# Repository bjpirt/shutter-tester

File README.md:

# Shutter Tester

A low cost but capable three-point shutter speed tester that runs on ESP32. It uses the PCB design to provide the physical structure of the tester so that all you need to do is solder it together and all of the mechanical design is taken care of.
It runs on ESP32 so is easily updated using the Arduino platform. The project is 100% open source (see the [license file](LICENSE.md) for details).
The UI runs in the browser and communicates with the shutter tester via Bluetooth - you can try out the UI [here](https://bjpirt.github.io/shutter-tester/?demo=true).

## Design

The design of the shutter tester is quite simple; it uses three IS485E / IS486E light sensors with built-in amplifiers to trigger three digital input interrupts on the ESP32 MCU. I wanted to keep the front side of the PCB clear to avoid it ever scratching the camera body so have opted for using surface mount components. I've used quite large packages for these so that they can be more easily hand soldered. The ESP32 uses an "ESP32 C3 Super Mini" module which is very small, can be surface mounted and has USB C built-in which can be used to power the whole board. I've kept the PCB size down to 50mm so that you can take advantage of low cost PCB fabrication. There are silk-screen markings to help position the tester over the camera shutter and three large holes to help see the edges from behind. It should either be taped in place or held with an elastic band.

The sensor has a Bluetooth connection and you can connect this to Chrome to use quite a capable web interface so you can get a lot of detail on the calibration. You can try out the UI [here](https://bjpirt.github.io/shutter-tester/?demo=true)

## Bill of materials

The BoM is quite low cost and relatively minimal:

- 1 x ESP32 C3 Super Mini module
- 3 x IS485E light sensor
- 6 x 1k 1206 SMD Resistor
- 3 x 2k 1206 SMD Resistor
- 3 x 0.01uF 1206 SMD Capacitor

## Assembly

The main thing to take care over during assembly is to ensure the lens of the light sensor aligns to the small hole in the PCB that allows the light through. The three legs of the sensor should be bent down slightly so that they can solder onto the three pads on the PCB.

The capacitors and resistors can be easily hand soldered (a finer soldering iron tip helps here) by applying solder to one of the pads on the PCB, using tweezers, solder one end of the component to the soldered pad on the PCB, then solder the other end once it is held in place. If you're experienced in surface mounting you could always use solder paste, but it's pretty straightforward without this. There are markings on the board for which component goes where (C1, C2 and C3 for the capacitors, Resistor values are marked 1k and 2k). The capacitors are optional and may be removed in a future iteration.

It's best to test the ESP32 module before soldering to ensure it's working fine. Program this using the sketch included and make sure it is outputting "Ready to measure" on the serial console (running at 921600 baud).

It's a good idea to place some black insulation tape over the back of the sensors otherwise stray light can cause false readings.

## Usage

Attach the shutter tester behind the shutter of the camera (I normally use 2 - 3 small blobs of Blu-Tak which works well). You can use the three larger holes in the tester to align with the edges of the shutter aperture. Open the shutter once you've this so you can check it's properly positioned by setting the shutter to "Bulb" and opening it. Remove the lens (if possible) and place a strong, even light at the front of the camera. You can use a full size bulb for this so long as it is the type that has a white diffuser bulb, not clear. Basically you want to ensure that light can pass directly through the three holes to reach the sensors, not at an angle. I've also had good results with a small USB powered LED panel.

### Using Bluetooth

There is a user interface that connects to the ESP32 from a Chrome web browser directly and lets you analyse all of the measurements quite easily.

You can easily use the [latest version](https://bjpirt.github.io/shutter-tester/). You should then be able to click the `Connect` button and pair with your shutter tester using Bluetooth. Select the speed you want to test, set up the light and fire the shutter. The new reading should appear in the table.

If you want to just try out the UI without a tester, you can use [this link](https://bjpirt.github.io/shutter-tester/?demo=true) and the "Test" button will simulate a shutter being fired. From a privacy perspective, the UI runs entirely in your browser and nothing goes over the internet.

If you want to run this locally you can do the following:

- Install Node.js (v22)
- Open a terminal in the `ui` folder of this repository
- run `npm install`
- run `npm run dev`
- Go to the URL printed in your terminal ([http://localhost:5173/](http://localhost:5173/))

### Using serial

Open a serial terminal to the ESP32 (this is built in to the Arduino IDE). You'll need to connect at 921600 baud.

Fire the shutter and it will print out the timings to the serial console. There are two sets of timings:

- The time taken for each shutter to travel across the frame - it's important to try and get both shutters moving at around the same speed
- The time each sensor was exposed for in microseconds, milliseconds and fractions of a second

```
Ready to measure

Shutter timing
Shutter 1: 1-2: 16582 uS || 2-3: 12632 uS
Shutter 2: 1-2: 23756 uS || 2-3: 18462 uS

Exposure timing
Sensor 1: 4346 uS || 4.3 mS || 1 / 228
Sensor 2: 5028 uS || 5.0 mS || 1 / 198
Sensor 3: 5528 uS || 5.5 mS || 1 / 182
```

In this example, the time taken for the first shutter to travel between the first and second (centre) sensors was 16582 microseconds and 12632 microseconds between the second (centre) and third sensor. You can see that in this example the second shutter is slow and would need adjusting.

Looking at the exposure time at each sensor, you can see the timings would need adjusting to give a good even exposure. First you would adjust the shutter timings to try and get them similar and then adjust both shutter tensioners to get the exposure time to match the expected (in this case it should have been 1/250 S)

# To Do

- [ ] Calculate variations across shutter and whether they are within tolerances
- [ ] Add graph visualisation of shutter speeds
- [ ] Generate report from three point test
- [x] Enable detailed measurements to be shown / hidden in three point mode
- [x] Deploy to GitHub pages using GitHub actions
- [x] Automatically work out vertical or horizontal shutter
- [x] Display full shutter timing
- [x] Separate shutter timing mode
- [x] Single shot mode (only show last shot timing) - useful for initial tuning
- [x] Compensation for sensor width

## Future

- [ ] Add persistence in the browser to enable common presets to be stored - e.g. camera types with speeds
- [ ] Enable different "runs" to be stored and compared so you can see progression when adjusting
- [ ] Add exposure measurement with light to frequency sensor
- [ ] Investigate reflective measurement from front of camera for e.g. Barnack Leicas
- [ ] Investigate using an analog photodiode instead of a binary sensor

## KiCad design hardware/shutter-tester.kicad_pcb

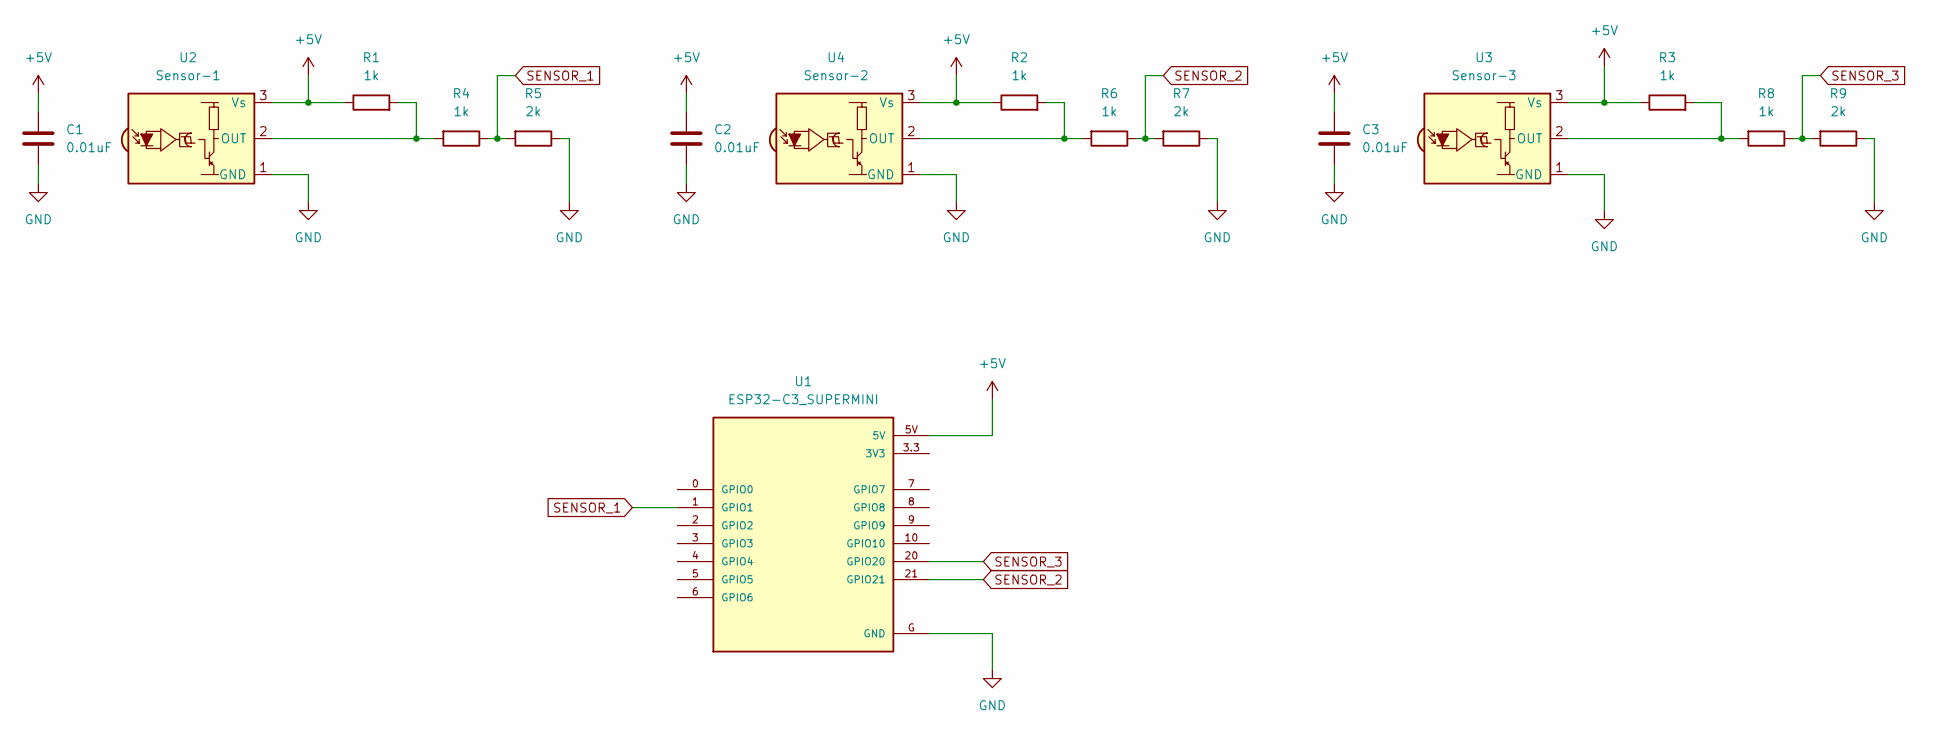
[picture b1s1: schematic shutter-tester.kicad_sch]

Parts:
C1, C2, C3: 0.01uF; C_1206_3216Metric_Pad1.33x1.80mm_HandSolder
R1, R2, R3, R4, R6, R8: 1k; R_1206_3216Metric_Pad1.30x1.75mm_HandSolder
R5, R7, R9: 2k; R_1206_3216Metric_Pad1.30x1.75mm_HandSolder
U1: ESP32-C3_SUPERMINI; MODULE_ESP32-C3_SUPERMINI_SMT
U2: Sensor-1; Sharp_IS485_Flat_Mount
U3: Sensor-3; Sharp_IS485_Flat_Mount
U4: Sensor-2; Sharp_IS485_Flat_Mount

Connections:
+5V: C1.2, C2.1, C3.2, R1.1, R2.1, R3.1, U1.5V, U2.3 (Vs), U3.3 (Vs), U4.3 (Vs)
GND: C1.1, C2.2, C3.1, R5.1, R7.1, R9.1, U1.G (GND), U2.1 (GND), U3.1 (GND), U4.1 (GND)
unnamed: R1.2, R4.2, U2.2 (OUT)
unnamed: R3.2, R8.2, U3.2 (OUT)
unnamed: R2.2, R6.2, U4.2 (OUT)
SENSOR_1: R4.1, R5.2, U1.1 (GPIO1)
SENSOR_2: R6.1, R7.2, U1.21 (GPIO21)
SENSOR_3: R8.1, R9.2, U1.20 (GPIO20)

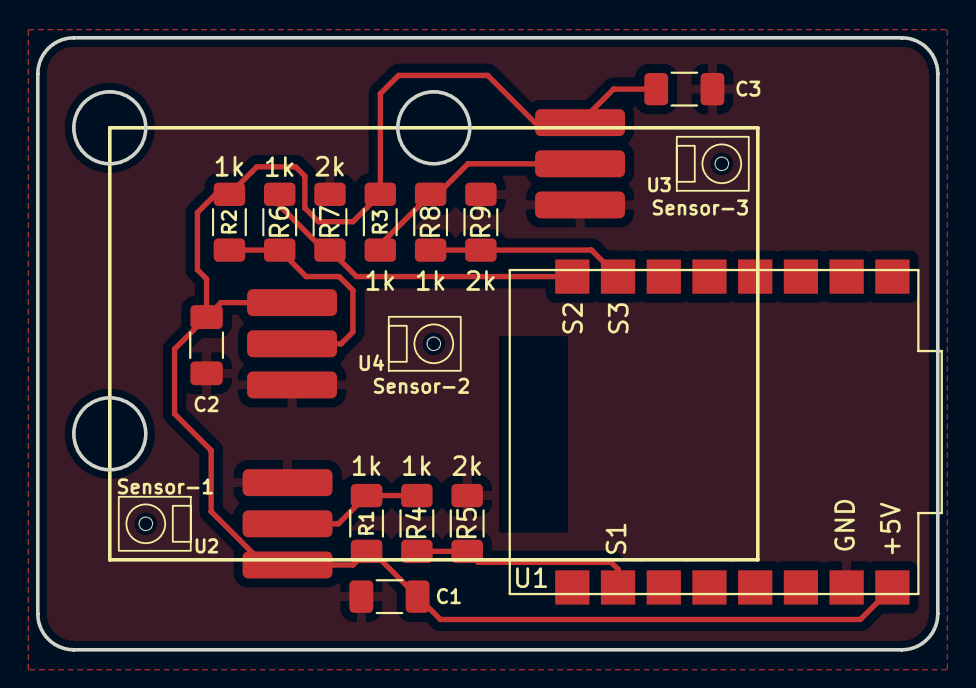
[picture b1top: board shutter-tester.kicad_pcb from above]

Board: 2 copper layers, 50.0 x 34.0 mm, 16 parts (0 on the bottom side), 8 nets.

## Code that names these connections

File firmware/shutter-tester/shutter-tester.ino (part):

#define LED 8
#define SENSOR_1 1
#define SENSOR_2 21
#define SENSOR_3 20

#define VERSION "2.2.0"

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  Serial.println("");
  Serial.println("Ready to measure");
  pinMode(LED, OUTPUT);
  pinMode(SENSOR_1, INPUT);
  pinMode(SENSOR_2, INPUT);
  pinMode(SENSOR_3, INPUT);
  attachInterrupt(SENSOR_1, sensor1_isr, CHANGE);
  attachInterrupt(SENSOR_2, sensor2_isr, CHANGE);
  attachInterrupt(SENSOR_3, sensor3_isr, CHANGE);
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
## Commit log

2025-01-24 Initial commit of project
2025-01-27 fix: groundplane issue w/ 2 via in PCB; update pictures
2025-01-28 v2.0 of the hardware
2025-01-31 Initial spike of Web Bluetooth UI
2025-01-31 Don't use GPIO 0 for sensor input
2025-02-18 More detail on the measurements
2025-02-18 Add ability to reset all measurements and clear individual ones
2025-02-18 v2.1 of the PCB
2025-02-22 Add the bluetooth firmware
2025-02-22 Add a header to the ui
2025-02-22 Rework the data display to use a single table
2025-03-02 Update the docs for the bluetooth UI
2025-03-02 Initial changes to support different modes for the shutter tester
2025-03-03 Enable the mode to be set on the sensor via Bluetooth
2025-03-06 Add to do list in Readme
2025-03-06 Change the page title from the default
2025-03-06 Display one decimal place in 1/X s timing display for accuracy
2025-03-06 Use 'timing' instead of 'data'
2025-03-07 Add initial implementation of sensor width compensation
2025-03-21 Add in full side to side shutter timings
2025-03-21 Fix the compensation algorithm and make it apply to summary rows
2025-03-21 Refactor the three point measurements page to be more self contained
2025-03-22 Wire up the different pages with an internal message bus
2025-03-22 Add shutter timing view and reorganise the settings
2025-03-22 Add a shot by shot mode
2025-04-10 Enable the shutter direction to be set for accurate compensation
2025-07-07 Create deploy-ui
    Set up GitHub actions to deploy the UI to GitHub pages
2025-07-07 Set the vite base directory
2025-07-07 Name the github actions file correctly
2025-07-07 Get github actions working
2025-07-07 Fix linting errors
2025-07-07 Update the readme

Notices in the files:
hardware/shutter-tester.kicad_pcb:
© Ben Pirt
